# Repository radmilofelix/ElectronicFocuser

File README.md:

# ElectronicFocuser
 Electronic focuser with stepper motor for telescopes

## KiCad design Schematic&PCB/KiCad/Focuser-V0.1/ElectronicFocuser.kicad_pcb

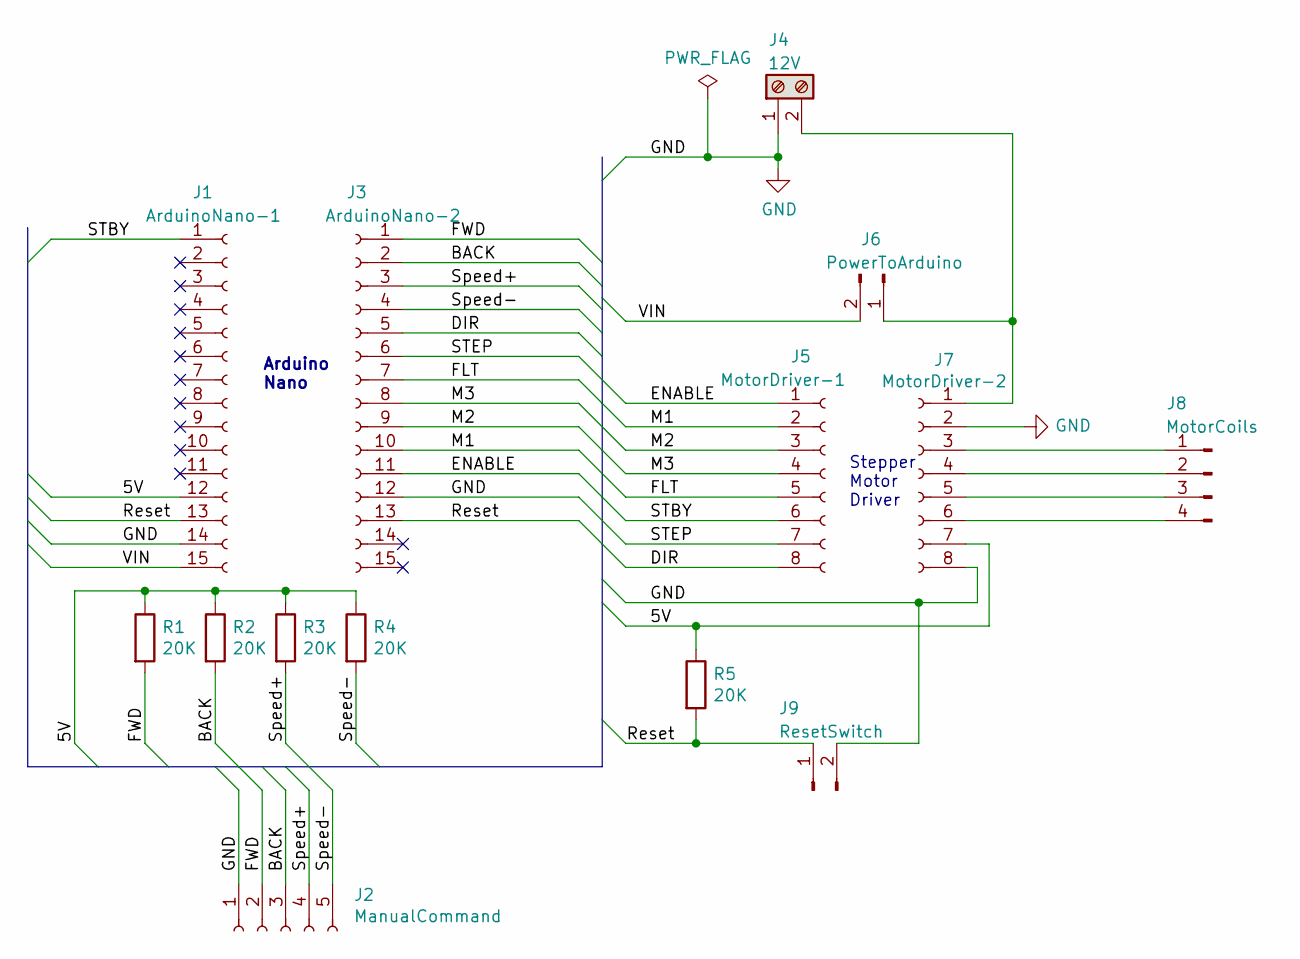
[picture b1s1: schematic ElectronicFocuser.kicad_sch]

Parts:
J1: ArduinoNano-1; PinHeader_1x15_P2.54mm_Vertical
J2: ManualCommand; PinHeader_1x05_P2.54mm_Vertical
J3: ArduinoNano-2; PinHeader_1x15_P2.54mm_Vertical
J4: 12V; TerminalBlock_Phoenix_MKDS-1,5-2-5.08_1x02_P5.08mm_Horizont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
J5: MotorDriver-1; PinHeader_1x08_P2.54mm_Vertical
J6: PowerToArduino; PinHeader_1x02_P2.54mm_Vertical
J7: MotorDriver-2; PinHeader_1x08_P2.54mm_Vertical
J8: MotorCoils; PinHeader_1x04_P2.54mm_Vertical
J9: ResetSwitch; PinHeader_1x02_P2.54mm_Vertical
R1, R2, R3, R4, R5: 20K; R_Axial_DIN0204_L3.6mm_D1.6mm_P7.62mm_Horizontal

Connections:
/5V: J1.12, J7.7, R1.1, R2.1, R3.1, R4.1, R5.1
/BACK: J2.3, J3.2, R2.2
/DIR: J3.5, J5.8
/ENABLE: J3.11, J5.1
/FLT: J3.7, J5.5
/FWD: J2.2, J3.1, R1.2
/M1: J3.10, J5.2
/M2: J3.9, J5.3
/M3: J3.8, J5.4
/Reset: J1.13, J3.13, J9.1, R5.2
/STBY: J1.1, J5.6
/STEP: J3.6, J5.7
/Speed+: J2.4, J3.3, R3.2
/Speed-: J2.5, J3.4, R4.2
/VIN: J1.15, J6.2
GND: J1.14, J2.1, J3.12, J4.1, J7.2, J7.8, J9.2
unnamed: J4.2, J6.1, J7.1
unnamed: J7.3, J8.1
unnamed: J7.4, J8.2
unnamed: J7.5, J8.3
unnamed: J7.6, J8.4

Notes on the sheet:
Arduino Nano
Stepper Motor Driver

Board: 2 copper layers, 14 parts (0 on the bottom side), 21 nets, no tracks yet.

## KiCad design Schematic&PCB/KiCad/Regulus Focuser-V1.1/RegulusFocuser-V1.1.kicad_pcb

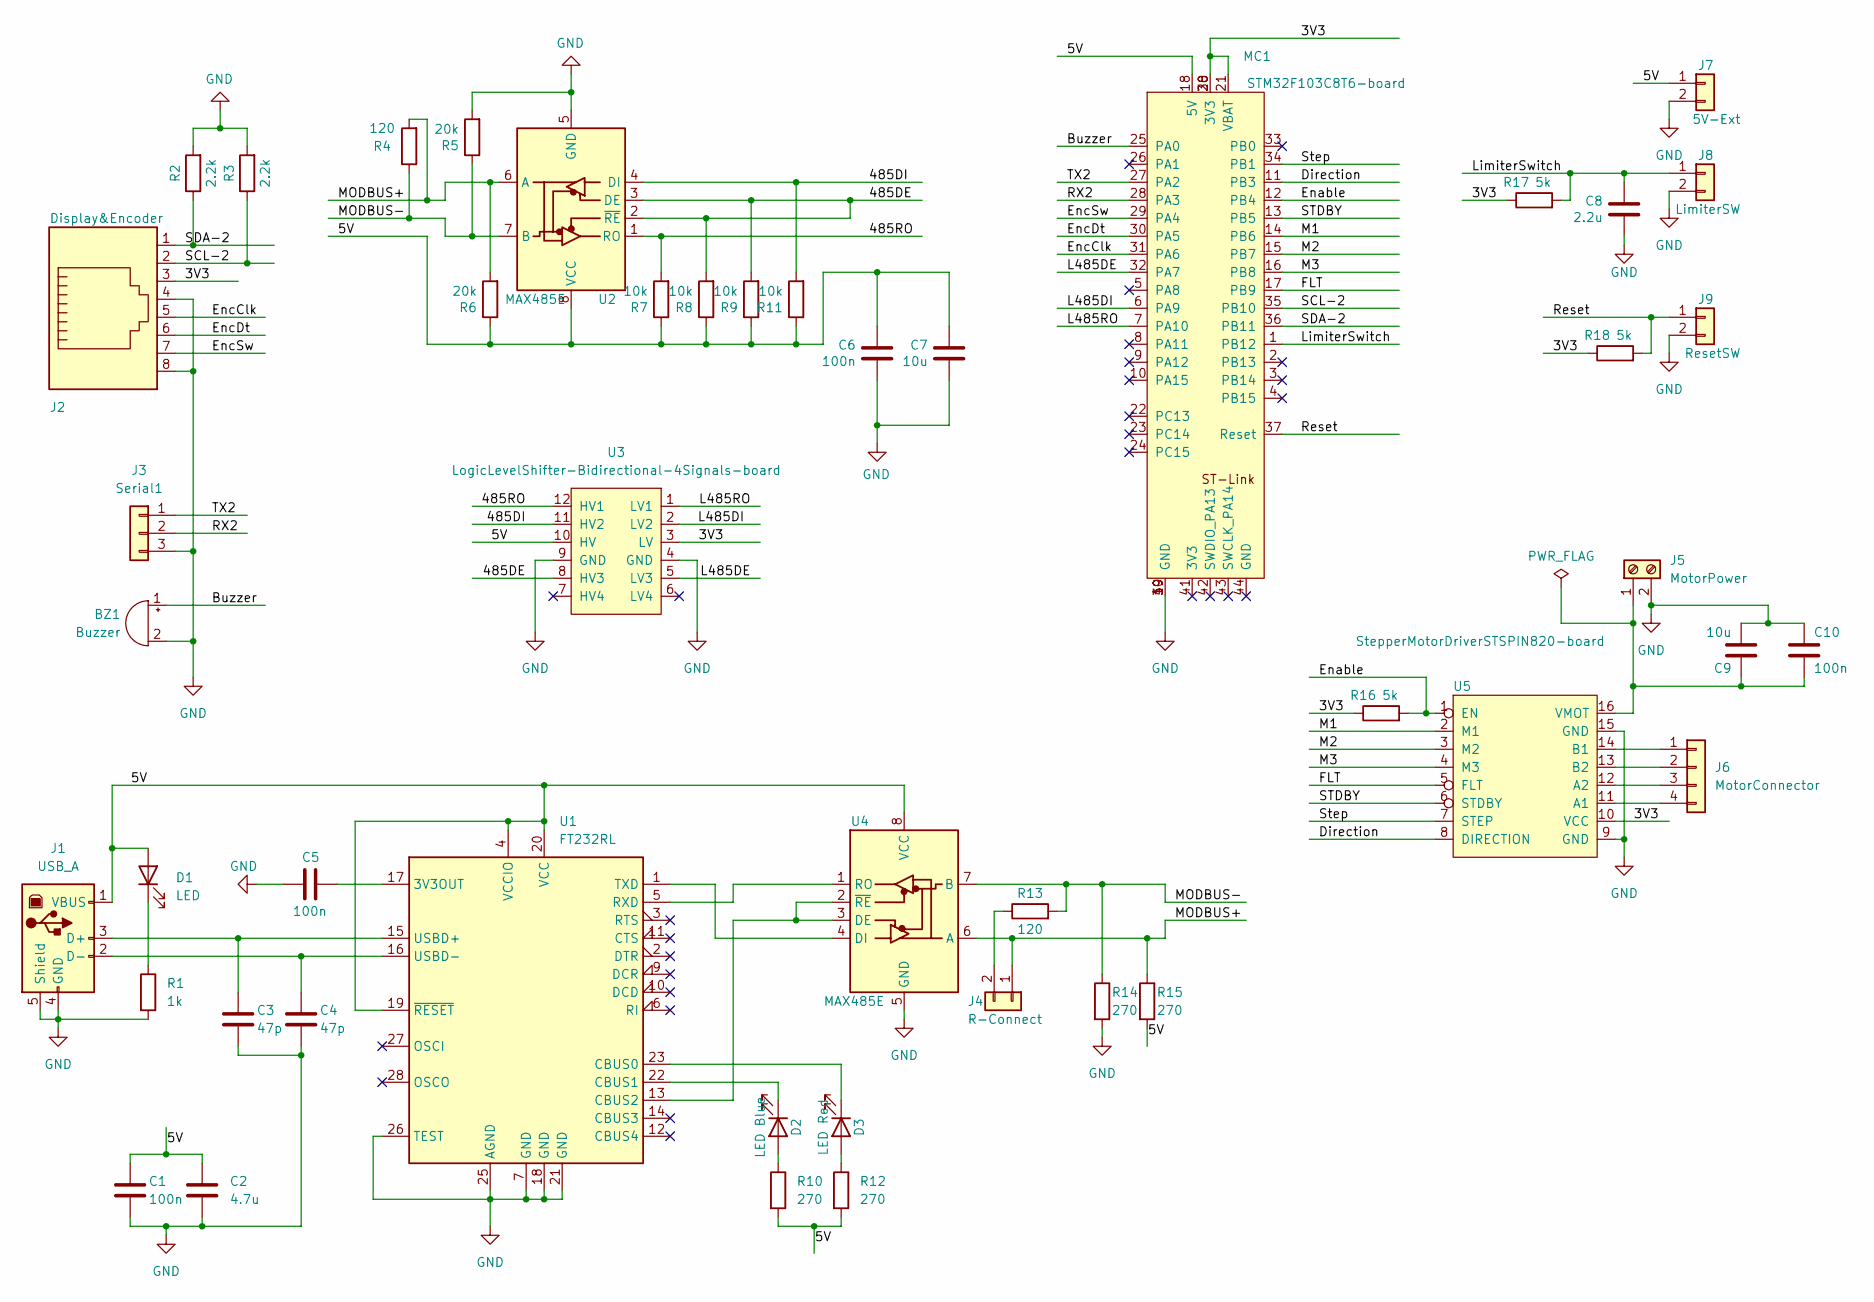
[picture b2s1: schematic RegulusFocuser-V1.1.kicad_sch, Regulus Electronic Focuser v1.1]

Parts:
BZ1: Buzzer; Buzzer-HSD-4pin
C1, C5, C6, C10: 100n; C_0805_2012Metric; LCSC C49678
C2: 4.7u; C_0805_2012Metric; LCSC C1779
C3, C4: 47p; C_0805_2012Metric; LCSC C14857
C7, C9: 10u; CP_EIA-3528-21_Kemet-B; LCSC C140404
C8: 2.2u; C_0805_2012Metric; LCSC C49217
D1: LED; LED_1206_3216Metric; LCSC C84270
D2: LED Blue; LED_0603_1608Metric; LCSC C84266
D3: LED Red; LED_0603_1608Metric; LCSC C2286
J1: USB_A; USB_B_Lumberg_2411_02_Horizontal
J2: Display&Encoder; RJ45_Amphenol_54602-x08_Horizontal
J3: Serial1; PinHeader_1x03_P2.54mm_Vertical
J4: R-Connect; PinHeader_1x02_P2.54mm_Vertical
J5: MotorPower; TerminalBlock_PTR_AKZ950-2_P5.08mm_Vertical
J6: MotorConnector; PinHeader_1x04_P2.54mm_Vertical
J7: 5V-Ext; PinHeader_1x02_P2.54mm_Vertical
J8: LimiterSW; PinHeader_1x02_P2.54mm_Vertical
J9: ResetSW; PinHeader_1x02_P2.54mm_Vertical
MC1: STM32F103C8T6-board; STM32F103C8T6
R1: 1k; R_1206_3216Metric; LCSC C136873
R2, R3: 2.2k; R_1206_3216Metric; LCSC C325909
R4, R13: 120; R_1206_3216Metric; LCSC C175512
R5, R6: 20k; R_1206_3216Metric; LCSC C18003
R7, R8, R9, R11: 10k; R_1206_3216Metric; LCSC C269766
R10, R12, R14, R15: 270; R_1206_3216Metric; LCSC C25366
R16, R17, R18: 5k; R_1206_3216Metric; LCSC C327044
U1: FT232RL; SSOP-28_5.3x10.2mm_P0.65mm; LCSC C8690
U2, U4: MAX485E; SOIC-8_3.9x4.9mm_P1.27mm; LCSC C19738
U3: LogicLevelShifter-Bidirectional-4Signals-board; LogicLevelShifter_Bidirectional_4Signals
U5: StepperMotorDriverSTSPIN820-board; StepperMotorDriverSTSPIN820

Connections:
/3V3: J2.3, MC1.20 (3V3), MC1.21 (VBAT), MC1.38 (3V3), R16.1, R17.1, R18.1, U3.3 (LV), U5.10 (VCC)
/5V: C1.1, C2.1, C6.1, C7.1, D1.2 (A), J1.1 (VBUS), J7.1, MC1.18 (5V), R6.1, R7.1, R8.1, R9.1, R10.2, R11.1, R12.2, R15.2, U1.4 (VCCIO), U1.19 (~RESET), U1.20 (VCC), U2.8 (VCC), U3.10 (HV), U4.8 (VCC)
/485DE: R8.2, R9.2, U2.2 (~RE), U2.3 (DE), U3.8 (HV3)
/485DI: R11.2, U2.4 (DI), U3.11 (HV2)
/485RO: R7.2, U2.1 (RO), U3.12 (HV1)
/Buzzer: BZ1.1 (-), MC1.25 (PA0)
/Direction: MC1.11 (PB3), U5.8 (DIRECTION)
/Enable: MC1.12 (PB4), R16.2, U5.1 (EN)
/EncClk: J2.5, MC1.31 (PA6)
/EncDt: J2.6, MC1.30 (PA5)
/EncSw: J2.7, MC1.29 (PA4)
/FLT: MC1.17 (PB9), U5.5 (FLT)
/L485DE: MC1.32 (PA7), U3.5 (LV3)
/L485DI: MC1.6 (PA9), U3.2 (LV2)
/L485RO: MC1.7 (PA10), U3.1 (LV1)
/LimiterSwitch: C8.1, J8.1, MC1.1 (PB12), R17.2
/M1: MC1.14 (PB6), U5.2 (M1)
/M2: MC1.15 (PB7), U5.3 (M2)
/M3: MC1.16 (PB8), U5.4 (M3)
/MODBUS+: J4.1, R4.2, R6.2, R15.1, U2.6 (A), U4.6 (A)
/MODBUS-: R4.1, R5.1, R13.2, R14.1, U2.7 (B), U4.7 (B)
/RX2: J3.2, MC1.28 (PA3)
/Reset: J9.1, MC1.37 (Reset), R18.2
/SCL-2: J2.2, MC1.35 (PB10), R3.1
/SDA-2: J2.1, MC1.36 (PB11), R2.1
/STDBY: MC1.13 (PB5), U5.6 (STDBY)
/Step: MC1.34 (PB1), U5.7 (STEP)
/TX2: J3.1, MC1.27 (PA2)
GND: BZ1.2 (+), C1.2, C2.2, C3.2, C4.2, C5.2, C6.2, C7.2, C8.2, C9.2, C10.1, J1.4 (GND), J1.5 (Shield), J2.4, J2.8, J3.3, J5.2, J7.2, J8.2, J9.2, MC1.19 (GND), MC1.39 (GND), MC1.40 (GND), R1.2, R2.2, R3.2, R5.2, R14.2, U1.7 (GND), U1.18 (GND), U1.21 (GND), U1.25 (AGND), U1.26 (TEST), U2.5 (GND), U3.4 (GND), U3.9 (GND), U4.5 (GND), U5.9 (GND), U5.15 (GND)
unnamed: C3.1, J1.3 (D+), U1.15 (USBD+)
unnamed: C4.1, J1.2 (D-), U1.16 (USBD-)
unnamed: C5.1, U1.17 (3V3OUT)
unnamed: C9.1, C10.2, J5.1, U5.16 (VMOT)
unnamed: D1.1 (K), R1.1
unnamed: D2.1 (K), U1.22 (CBUS1)
unnamed: D2.2 (A), R10.1
unnamed: D3.1 (K), U1.23 (CBUS0)
unnamed: D3.2 (A), R12.1
unnamed: J4.2, R13.1
unnamed: J6.1, U5.14 (B1)
unnamed: J6.2, U5.13 (B2)
unnamed: J6.3, U5.12 (A2)
unnamed: J6.4, U5.11 (A1)
unnamed: U1.1 (TXD), U4.4 (DI)
unnamed: U1.5 (RXD), U4.1 (RO)
unnamed: U1.13 (CBUS2), U4.2 (~RE), U4.3 (DE)

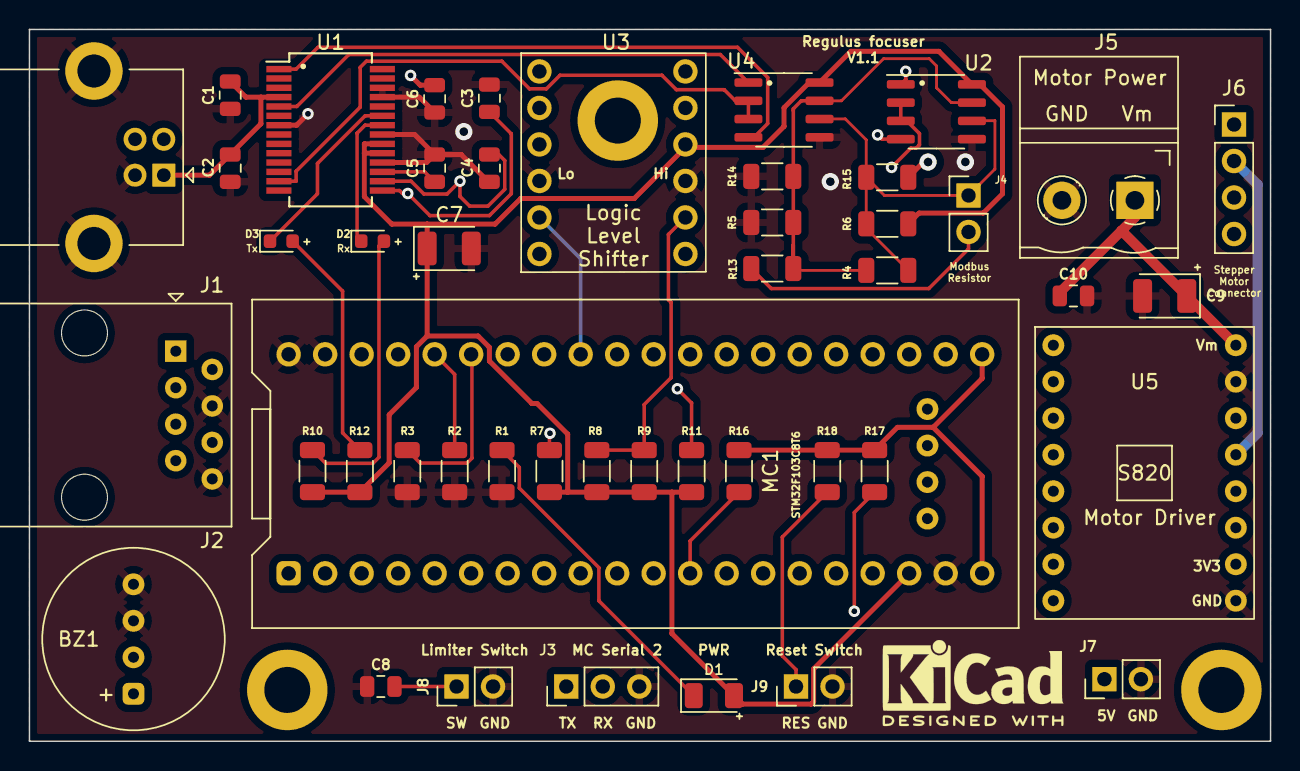
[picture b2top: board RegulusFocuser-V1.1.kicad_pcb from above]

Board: 4 copper layers, 86.4 x 49.5 mm, 50 parts (0 on the bottom side), 46 nets.

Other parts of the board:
MH1, MH2, MH3: MountingHole_3.2mm_M3_DIN965_Pad

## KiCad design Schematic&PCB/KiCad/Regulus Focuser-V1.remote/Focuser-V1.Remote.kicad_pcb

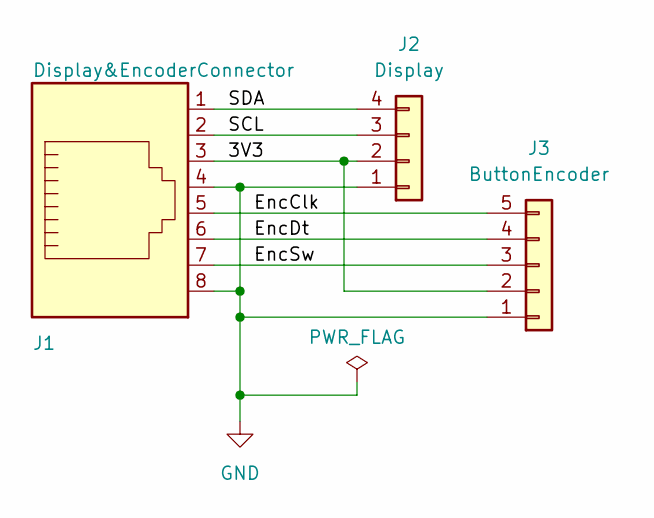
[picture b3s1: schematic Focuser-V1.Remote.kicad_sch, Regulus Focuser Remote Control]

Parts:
J1: Display&EncoderConnector; RJ45_Amphenol_54602-x08_Horizontal
J2: Display; PinHeader_1x04_P2.54mm_Vertical
J3: ButtonEncoder; PinHeader_1x05_P2.54mm_Vertical

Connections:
/3V3: J1.3, J2.2, J3.2
/EncClk: J1.5, J3.5
/EncDt: J1.6, J3.4
/EncSw: J1.7, J3.3
/SCL: J1.2, J2.3
/SDA: J1.1, J2.4
GND: J1.4, J1.8, J2.1, J3.1

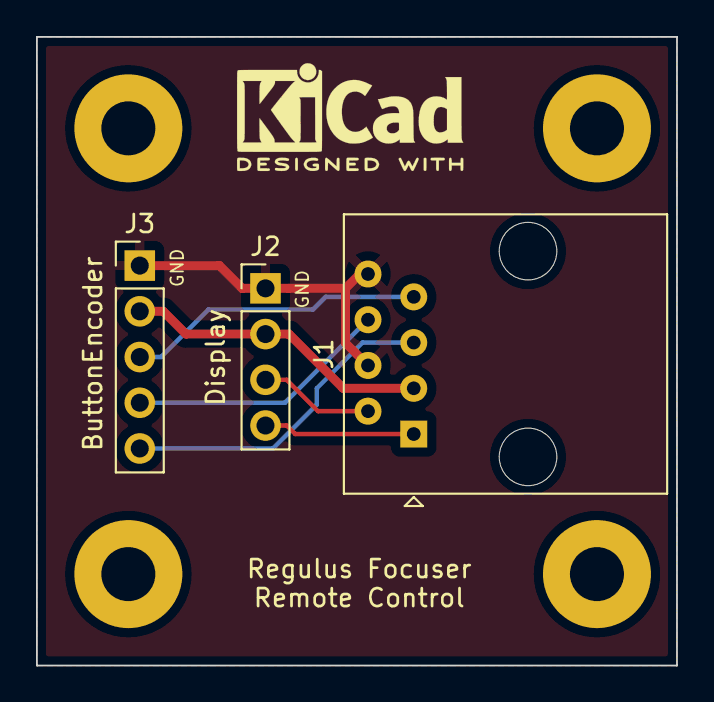
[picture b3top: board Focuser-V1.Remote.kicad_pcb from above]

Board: 2 copper layers, 35.6 x 34.9 mm, 7 parts (0 on the bottom side), 7 nets.

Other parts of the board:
REF1, REF2, REF3, REF4: MountingHole_3mm_Pad

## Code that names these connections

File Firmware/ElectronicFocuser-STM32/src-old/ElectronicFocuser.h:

#include <Arduino.h>
#include <Adafruit_SSD1306.h>
#include "modbusSlave.h"

#define EN  PB4     
#define M1  PB6 // A4988 MS1; DRV8825 M0; STSPIN220 MODE1; STSPIN820 M1       
#define M2  PB7 // A4988 MS2; DRV8825 M1; STSPIN220 MODE2; STSPIN820 M2 
#define M3  PB8 // A4988 MS3; DRV8825 M2; STSPIN220 (1); STSPIN820 M3 
#define STDBY  PB5
#define STEP  PB1
#define DIR  PB3
#define RESET PB5


#define SCREEN_WIDTH 128 // OLED display width, in pixels
#define SCREEN_HEIGHT 64 // OLED display height, in pixels


// Modbus
//#define REGROOFPOSITION				0
//#define REGCOMMANDFROMPI			1
//#define REGRESPONSETOPI				2
//#define REGSTATUS                   3 // Motor Enabled/Disabled



//  Use I2C-1
//Adafruit_SSD1306 display(SCREEN_WIDTH, SCREEN_HEIGHT, &Wire, -1);

//  Use I2C-2
TwoWire Wire1(PB11, PB10);// Use STM32 I2C2
Adafruit_SSD1306 display(SCREEN_WIDTH, SCREEN_HEIGHT, &Wire1, -1);
HardwareSerial Serial2(USART2);   // PA3  (RX)  PA2  (TX)

void setup();
void loop();
void displayMenu();
int pulseStep (unsigned long numberOfSteps, int motionDirection, int duration);
int toneStep (unsigned long numberOfSteps, int motionDirection, unsigned long frequency);
unsigned long readNumber();
void ValidateMicrostepMode();
void displayValues();
void operationSelect();
void selectMicrostepMode(int microstep);

//*
void displaySize1Text();
void displaySize2Text();
void displaySize1Char(char* txt, int x, int y, bool eraseDisplay);
void displaySize2Char(char* txt, int x, int y, bool eraseDisplay);
//*/

ModbusSlave modbus_f(1,Serial1,PA7);

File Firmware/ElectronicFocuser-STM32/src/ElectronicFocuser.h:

//#include <Arduino.h>
#include "ModbusSlave.h"
#include <Adafruit_SSD1306.h>
#include <RotaryEncoder.h>
#include "OneButton.h"
#include "FocuserStepper.h"
#include "FocuserDefinitions.h"

#define ENCODER_CLK PA6
#define ENCODER_DT PA5
#define ENCODER_SW  PA4
#define BUZZERPIN PA0

#define SCREEN_WIDTH 128 // OLED display width, in pixels
#define SCREEN_HEIGHT 64 // OLED display height, in pixels

//  Use I2C-1
//Adafruit_SSD1306 display(SCREEN_WIDTH, SCREEN_HEIGHT, &Wire, -1);

//  Use I2C-2
TwoWire Wire1(PB11, PB10);// Use STM32 I2C2
Adafruit_SSD1306 display(SCREEN_WIDTH, SCREEN_HEIGHT, &Wire1, -1);
HardwareSerial Serial2(USART2);   // PA3  (RX)  PA2  (TX)

void setup();
void loop();
void LimitSwitchInterrupt();
void MotorInit();
void FocuserInit();
void SyncToZero();
void GetFlashVar();
void SetFlashVar(byte flashValue);

#ifdef DEBUG
void DisplayMenu();
void DisplayFocuserData();
unsigned long ReadNumber();
void DisplayValues();
void KeyboardOperationSelect();
#endif

void SignalBeeps( int nbeeps, int beepFreq);
void Signal2Beep1();
void Signal2Beep2();
void SignalBeep1();
void SignalBeep2();
void SignalBeep3();

void DisplayMessageInitStartMessage();
void DisplayMessageInitStage1();
void DisplayMessageInitCanNotReachZero();
void DisplayMessageInitStage2();
void DisplayMessageInitCanNotReachMax();
void DisplayMessageInitStage3();
void DisplayMessageFocuserFault();
void DisplayMessageClearFocuserFault();
void DisplayMessageInitEarlyZero();
void DisplayMessageInitStage4();
void DisplayMessageInitErrorSlipping();
void DisplayMessageZeroSync();
void DisplayFocuserData();
void DisplayRefresh();

void ModbusPoll();
void CommandProcessor();

///////////////////////////////////////////////// Encoder callbacks ////////////////////////////////////////////////////////////////////////////////
void CheckTicks();
void SingleClick();
void DoubleClick();
void MultiClick();
void PressStart();
void PressStop();
static int pos = 0;
/////////////////////////////////////////////////////////////////////////////////////////////////////////////////////////////////

bool notInit = true;
bool interruptTriggered = false;
bool remoteControlEnabled = true;
byte focuserFault = 0;
unsigned long PressStartTime, cycleTime;
bool longPress=false;
int longClickCycles=0;
int longClickCycleTime=100; // ms
long lostSteps; // step difference when focuser hits the limit switch at 0 position
int working=0;
unsigned int previousPress = 0;
int contactDebounce = 400;
int variableTextSize = 2;

RotaryEncoder *encoder = nullptr;
OneButton button(ENCODER_SW, true);
ModbusSlave modbus_f(1,Serial1,PA7);
FocuserStepper fstepper;

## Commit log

2023-07-04 Folders reorganisation
2023-07-16 reorganising
2023-08-17 I2C pullup resistors are connected wrong
2023-08-17 cleanup
2023-10-01 cleaned the code
2023-10-31 updated .gitignore
2023-12-25 Added mechanical designs for low profile rack and pinion focuser
2023-12-28 Added low profile rack and pimion focuser
    Added code and design for low profile rack and pinion focuser.
    Focuser fault state is now saved in the flash memory.
2024-01-01 Increased FocusAbsPosN[0].max to 5000000 in initProperties()
2024-06-15 updated INDI driver to indilib 2.8.0
